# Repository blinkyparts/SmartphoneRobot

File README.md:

# Smartphone Robot - An easy robot you can control with your Smartphone

This is an easy robot soldering kit to turn a smartphone into a robot. The fun part is, you don't program the hardware. You just add an Smartphone and due to light signals it controlls the motors of the robot. Thus you can easily controll the robot with any smartphone wihtout any programming skills. You want to take it further? No problem. We also have [coding tutorials](https://www.voltpaperscissors.com/diyroboticsplattform#aiintro) to program your own app.

## Where to Buy?
You can purchase the Smartphone Robot kit in our online store:

➡️ [Buy the Smartphone Robot Kit Here]()

## Features
- **Easy soldering kit** – Perfect for beginners
- **Innovative mechanism** – Control your robot by light
- **Turn a smartphone into a robot** - Old phone? No problem. Turn it into a fun little robot
- **Emotions for your robot** - You can also program emotions to your robot! Make it sweet!

## Included in the Kit
| Quantity  | Description 									|
|:---------:|:----------------------------------------------|
| 1 		| PCB 											|
| 1 		| Battery Holder 3xAA 							|
| 1 		| LED 3mm green 								|
| 2 		| LDR (Light Sensor) 							|
| 2 		| Motors 										|
| 1 		| Push Button 									|
| 2 		| 10k Motor Resistor 							|
| 1 		| 1k LED Resistor 								|
| 2 		| Mosfet IRLB8721 								|
| 13 		| Lasercut Wooden Parts 						|
| 2			| Rubber Ring (68mm) 							|
| 4			| Wire (12cm)									|
| 1 		| Teflon Slider 								|
| 2			| AA-/Mignon-Batteries (Recarchable)			|
| 1 		| Plastic Cap of an PET Bottle (not included) 	|
| 4			| Zip Tie (not included)						|

## Needed tools (not included)
- Wood glue
- Hot glue
- Soldering iron

## Wooden part
We've used the wonderful boxes generator from the hackspace-bamberg.de: https://boxes.hackerspace-bamberg.de/
We also use 3mm plywood. You can find the laser-files in this repository.

## Assembly Instructions
For assembly, you will need:

A detailed **step-by-step guide** is available in the Wiki and GitHub repository.

## License
This project is licensed under **[CC-BY-NC-SA 4.0](https://creativecommons.org/licenses/by-nc-sa/4.0/)** - [Volt, Paper, Scissors!](https://www.voltpaperscissors.com/) and [Timo Schindler](https://shop.blinkyparts.com)

**Happy Soldering! 🚀🥚**

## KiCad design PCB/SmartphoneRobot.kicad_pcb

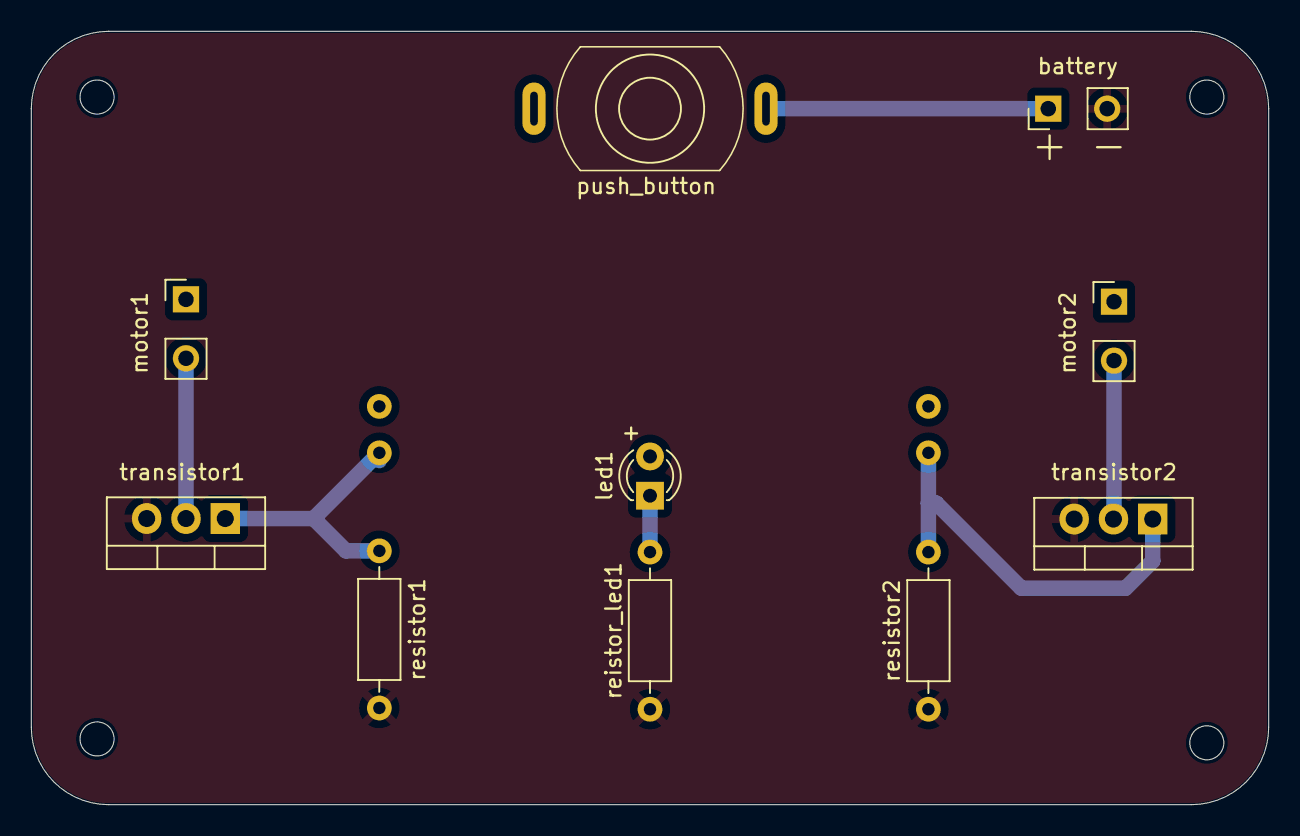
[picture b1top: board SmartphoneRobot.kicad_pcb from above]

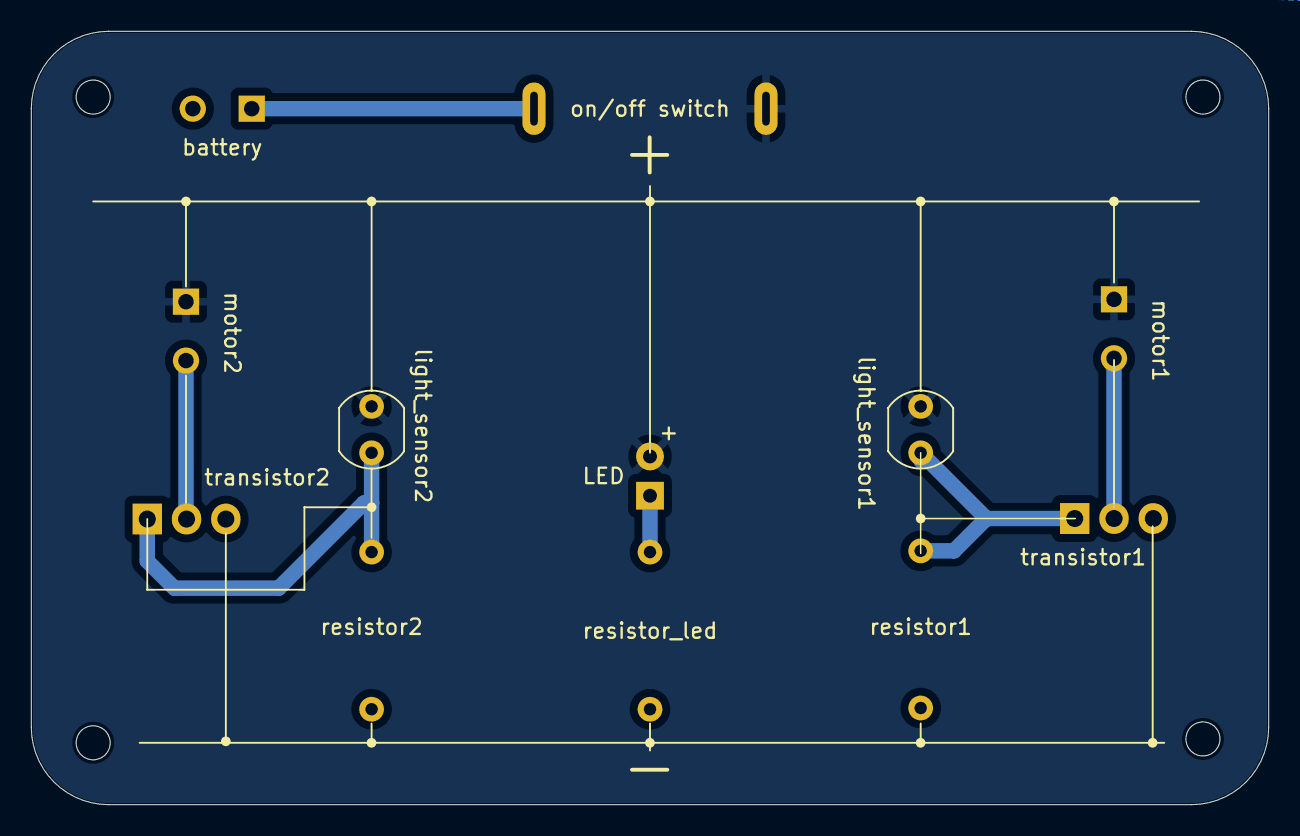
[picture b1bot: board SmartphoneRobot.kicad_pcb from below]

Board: 2 copper layers, 80.0 x 50.0 mm, 17 parts (5 on the bottom side), 8 nets.

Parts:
battery: battery; PinHeader_1x02_P2.54mm_Vertical_wider
ce-symbol_mask_3mm: G***; ce-icon_3mm
led1: LED; LED_D3.0mm
light_sensor1, light_sensor2: A9013; R_LDR_5.0x4.1mm_P3mm_Vertical
motor1: motor1; PinHeader_1x02_P2.54mm_Vertical_wider
motor2: motor2; PinHeader_1x02_P2.54mm_Vertical_wider
pfeil_1_4mm: G***; pfeile_pfeil1_4mm
pfeil_2_4mm: G***; pfeile_pfeil2_4mm
push_button: on/off switch; Push_Button_THT
reistor_led1: 20k; R_Axial_DIN0207_L6.3mm_D2.5mm_P10.16mm_Horizontal
resistor1, resistor2: 20k; R_Axial_DIN0207_L6.3mm_D2.5mm_P10.16mm_Horizontal
rohs-symbol_mask_3mm: G***; rohs-icon_3mm
transistor1: transistor1; TO-220-3_Vertical
transistor2: transistor2; TO-220-3_Vertical
weee-symbol_mask_3mm: G***; weee-icon_3mm

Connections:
+6V: battery.1 (+), push_button.2
GND: battery.2 (-), reistor_led1.1, resistor1.1, resistor2.1, transistor1.3 (S), transistor2.3 (S)
unnamed: led1.1 (K), reistor_led1.2
unnamed: motor1.2 (-), transistor1.2 (D)
unnamed: motor2.2 (-), transistor2.2 (D)
unnamed: light_sensor1.2, resistor1.2, transistor1.1 (G)
unnamed: light_sensor2.2, resistor2.2, transistor2.1 (G)
VCC: led1.2 (A), light_sensor1.1, light_sensor2.1, motor1.1 (+), motor2.1 (+), push_button.1

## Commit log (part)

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2025-03-26 added gitignore
2025-03-26 inital commit for version 1.2
2025-03-26 added license-file
2025-03-26 added readme and pictures
2025-03-26 fixed some wording
2025-03-26 added laser parts
2025-03-26 changed license to cc-by-nc-sa 4.0
2025-03-26 added misc to gitignore
2025-03-26 minor fix
2025-03-27 added link to coding tutorials to README.md

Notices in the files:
PCB/SmartphoneRobot.kicad_pcb:
CC-BY-SA 4.0
